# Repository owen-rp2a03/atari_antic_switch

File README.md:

# Atari NTSC/PAL Antic switch board (Incomplete)

Theory - Uses two '245 transceivers and holds reset on either Antic to disable them; isolating the control signals may not be necessary but doing it just in case.
Too many wires and two dip-40 chips for me to reliably test on cheap breadboards, so designed a theoretical circuit for a prototype pcb.

2026-5-17 - Untested prototype design

2026-5-28 - Boards recieved from PCBWay, confirmed not working, signal directions through bus tranciever need reworking due to my uncertainty of the i/o of the control lines for Antic.

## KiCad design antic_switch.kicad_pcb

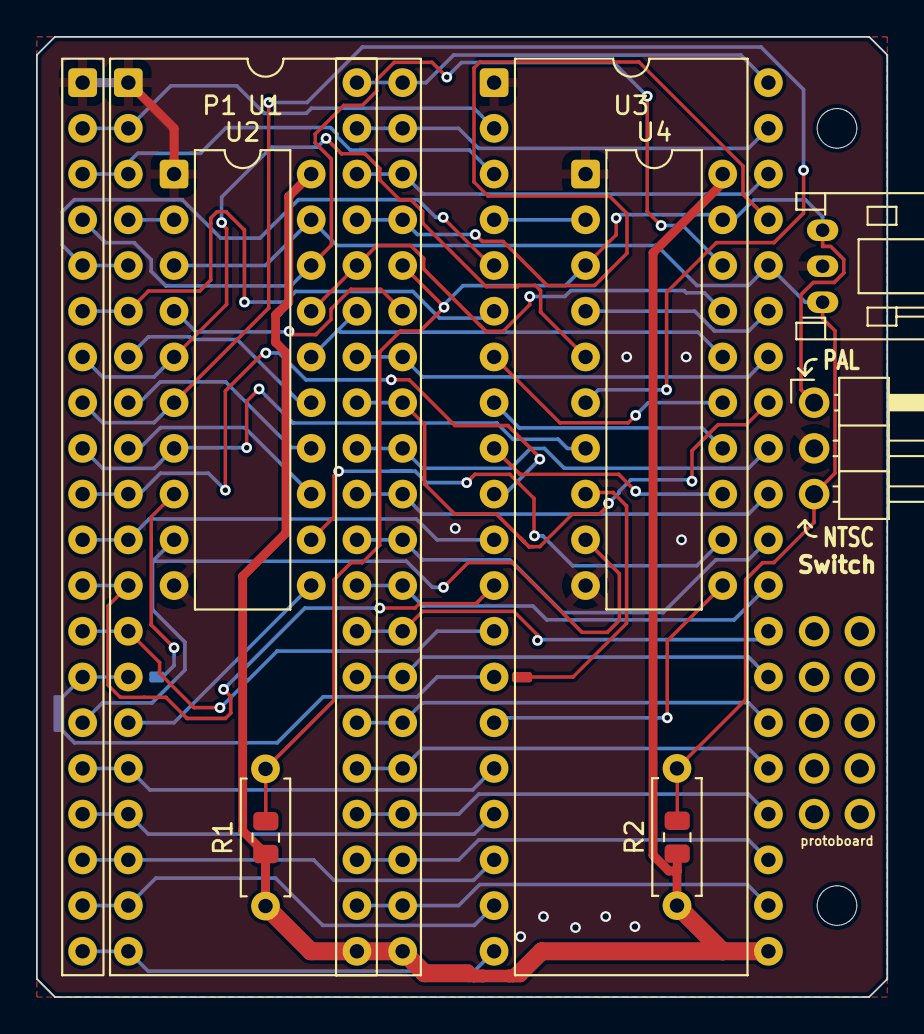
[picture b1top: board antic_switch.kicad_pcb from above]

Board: 2 copper layers, 47.2 x 53.3 mm, 12 parts (0 on the bottom side), 55 nets.

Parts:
J1: 2.54m; PinHeader_1x03_P2.54mm_Horizontal
J2: 2.00m; JST_PH_S3B-PH-K_1x03_P2.00mm_Horizontal
J3: 2.54; PinHeader_2x05_P2.54mm_Horizontal
MH1, MH2: MountingHole_2.2mm_M2
P1: ANTIC_Conn; DIP-40_W15.24mm
R1, R2: 10k; R_Axial_DIN0207_L6.3mm_D2.5mm_P7.62mm_Horizontal
U1: ANTIC_NTSC; DIP-40_W15.24mm
U2, U4: 74LS245; DIP-20_W7.62mm
U3: ANTIC_PAL; DIP-40_W15.24mm

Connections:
/FI0: P1.35 (FI0), U2.16 (B2), U4.16 (B2)
/R/~W: U2.12 (B6), U4.12 (B6)
/~HALT: P1.9 (~HALT), U2.7 (A5), U4.7 (A5)
/~LP: P1.4 (~LP), U2.18 (B0), U4.18 (B0)
/~NMI: P1.7 (~NMI), U2.5 (A3), U4.5 (A3)
/~NTSC/P_OFF: J1.3, J2.1, R2.2, U2.3 (A1), U2.19 (CE), U3.36 (~RESET)
/~PAL/N_OFF: J1.1, J2.3, R1.2, U1.36 (~RESET), U4.3 (A1), U4.19 (CE)
/~READY: P1.15 (~READY), U2.9 (A7), U4.9 (A7)
/~REF: P1.8 (~REF), U2.6 (A4), U4.6 (A4)
/~RESET: P1.36 (~RESET), U2.17 (B1), U4.17 (B1)
GND: J1.2, J2.2, P1.1 (VSS), U1.1 (VSS), U2.1 (A->B), U2.10 (GND), U3.1 (VSS), U4.1 (A->B), U4.10 (GND)
unnamed: P1.13 (A0), U1.13 (A0), U3.13 (A0)
unnamed: P1.12 (A1), U1.12 (A1), U3.12 (A1)
unnamed: P1.11 (A2), U1.11 (A2), U3.11 (A2)
unnamed: P1.10 (A3), U1.10 (A3), U3.10 (A3)
unnamed: P1.28 (A4), U1.28 (A4), U3.28 (A4)
unnamed: P1.27 (A5), U1.27 (A5), U3.27 (A5)
unnamed: P1.26 (A6), U1.26 (A6), U3.26 (A6)
unnamed: P1.25 (A7), U1.25 (A7), U3.25 (A7)
unnamed: P1.24 (A8), U1.24 (A8), U3.24 (A8)
unnamed: P1.23 (A9), U1.23 (A9), U3.23 (A9)
unnamed: P1.16 (A10), U1.16 (A10), U3.16 (A10)
unnamed: P1.22 (A11), U1.22 (A11), U3.22 (A11)
unnamed: P1.17 (A12), U1.17 (A12), U3.17 (A12)
unnamed: P1.18 (A13), U1.18 (A13), U3.18 (A13)
unnamed: P1.19 (A14), U1.19 (A14), U3.19 (A14)
unnamed: P1.20 (A15), U1.20 (A15), U3.20 (A15)
unnamed: P1.2 (AN0), U1.2 (AN0), U3.2 (AN0)
unnamed: P1.3 (AN1), U1.3 (AN1), U3.3 (AN1)
unnamed: P1.5 (AN2), U1.5 (AN2), U3.5 (AN2)
unnamed: P1.30 (D0), U1.30 (D0), U3.30 (D0)
unnamed: P1.31 (D1), U1.31 (D1), U3.31 (D1)
unnamed: P1.32 (D2), U1.32 (D2), U3.32 (D2)
unnamed: P1.33 (D3), U1.33 (D3), U3.33 (D3)
unnamed: P1.40 (D4), U1.40 (D4), U3.40 (D4)
unnamed: P1.39 (D5), U1.39 (D5), U3.39 (D5)
unnamed: P1.38 (D6), U1.38 (D6), U3.38 (D6)
unnamed: P1.37 (D7), U1.37 (D7), U3.37 (D7)
unnamed: P1.14 (R/~W), U1.14 (R/~W), U3.14 (R/~W)
unnamed: P1.34 (o0), U1.34 (o0), U3.34 (o0)
unnamed: P1.29 (o2), U1.29 (o2), U3.29 (o2)
unnamed: P1.6 (~RNMI), U1.6 (~RNMI), U3.6 (~RNMI)
unnamed: U1.35 (FI0), U2.4 (A2)
unnamed: U1.9 (~HALT), U2.13 (B5)
unnamed: U1.4 (~LP), U2.2 (A0)
unnamed: U1.7 (~NMI), U2.15 (B3)
unnamed: U1.15 (~READY), U2.11 (B7)
unnamed: U1.8 (~REF), U2.14 (B4)
unnamed: U3.35 (FI0), U4.4 (A2)
unnamed: U3.9 (~HALT), U4.13 (B5)
unnamed: U3.4 (~LP), U4.2 (A0)
unnamed: U3.7 (~NMI), U4.15 (B3)
unnamed: U3.15 (~READY), U4.11 (B7)
unnamed: U3.8 (~REF), U4.14 (B4)
VCC: P1.21 (Vcc), R1.1, R2.1, U1.21 (Vcc), U2.20 (VCC), U3.21 (Vcc), U4.20 (VCC)

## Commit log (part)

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2026-05-16 gerber
2026-05-17 header for gtia clocks
2026-05-17 imgs
2026-05-31 complete rework
